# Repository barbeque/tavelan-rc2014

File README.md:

# Board files
Made using KiCad 8.0.3

# Current Status
Submitted to JLCPCB (June 2024) not tested yet.

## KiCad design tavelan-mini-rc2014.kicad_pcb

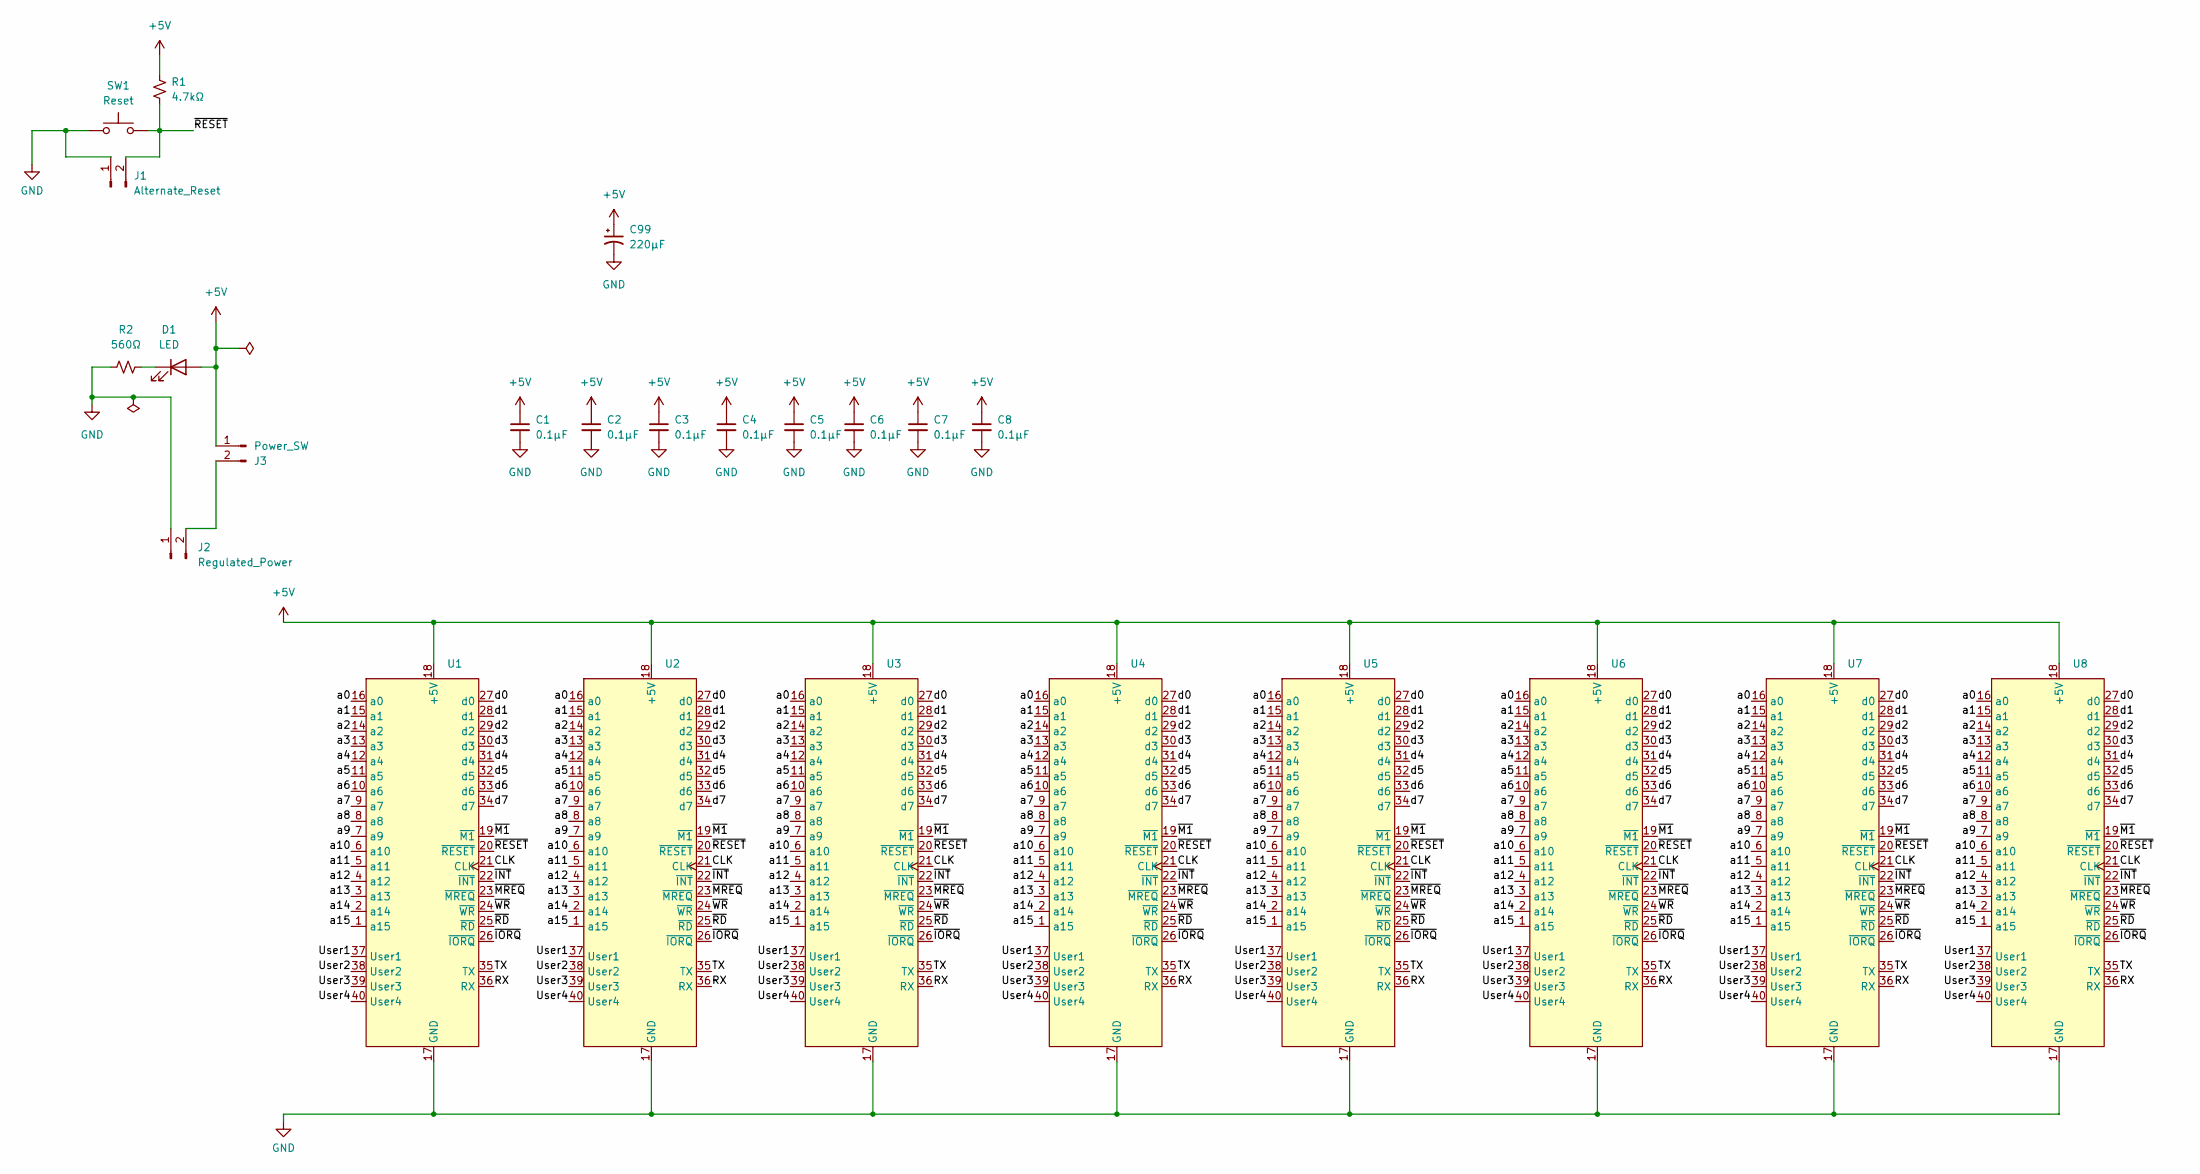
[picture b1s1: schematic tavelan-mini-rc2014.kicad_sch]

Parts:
C1, C2, C3, C4, C5, C6, C7, C8: 0.1µF; C_Disc_D5.0mm_W2.5mm_P5.00mm
C99: 220µF; CP_Radial_D8.0mm_P3.80mm
D1: LED; LED_D3.0mm
J1: Alternate_Reset; TerminalBlock_TE_282834-2_1x02_P2.54mm_Horizontal
J2: Regulated_Power; TerminalBlock_TE_282834-2_1x02_P2.54mm_Horizontal
J3: Power_SW; TerminalBlock_TE_282834-2_1x02_P2.54mm_Horizontal
R1: 4.7kΩ; R_Axial_DIN0207_L6.3mm_D2.5mm_P10.16mm_Horizontal
R2: 560Ω; R_Axial_DIN0207_L6.3mm_D2.5mm_P10.16mm_Horizontal
SW1: Reset; SW_PUSH_6mm
U1, U2, U3, U4, U5, U6, U7, U8: PinSocket_1x40_P2.54mm_Vertical

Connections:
+5V: C1.1, C2.1, C3.1, C4.1, C5.1, C6.1, C7.1, C8.1, C99.1, D1.2 (A), J3.1, R1.1, U1.18 (+5V), U2.18 (+5V), U3.18 (+5V), U4.18 (+5V), U5.18 (+5V), U6.18 (+5V), U7.18 (+5V), U8.18 (+5V)
/CLK: U1.21 (CLK), U2.21 (CLK), U3.21 (CLK), U4.21 (CLK), U5.21 (CLK), U6.21 (CLK), U7.21 (CLK), U8.21 (CLK)
/RX: U1.36 (RX), U2.36 (RX), U3.36 (RX), U4.36 (RX), U5.36 (RX), U6.36 (RX), U7.36 (RX), U8.36 (RX)
/TX: U1.35 (TX), U2.35 (TX), U3.35 (TX), U4.35 (TX), U5.35 (TX), U6.35 (TX), U7.35 (TX), U8.35 (TX)
/User1: U1.37 (User1), U2.37 (User1), U3.37 (User1), U4.37 (User1), U5.37 (User1), U6.37 (User1), U7.37 (User1), U8.37 (User1)
/User2: U1.38 (User2), U2.38 (User2), U3.38 (User2), U4.38 (User2), U5.38 (User2), U6.38 (User2), U7.38 (User2), U8.38 (User2)
/User3: U1.39 (User3), U2.39 (User3), U3.39 (User3), U4.39 (User3), U5.39 (User3), U6.39 (User3), U7.39 (User3), U8.39 (User3)
/User4: U1.40 (User4), U2.40 (User4), U3.40 (User4), U4.40 (User4), U5.40 (User4), U6.40 (User4), U7.40 (User4), U8.40 (User4)
/a0: U1.16 (a0), U2.16 (a0), U3.16 (a0), U4.16 (a0), U5.16 (a0), U6.16 (a0), U7.16 (a0), U8.16 (a0)
/a1: U1.15 (a1), U2.15 (a1), U3.15 (a1), U4.15 (a1), U5.15 (a1), U6.15 (a1), U7.15 (a1), U8.15 (a1)
/a2: U1.14 (a2), U2.14 (a2), U3.14 (a2), U4.14 (a2), U5.14 (a2), U6.14 (a2), U7.14 (a2), U8.14 (a2)
/a3: U1.13 (a3), U2.13 (a3), U3.13 (a3), U4.13 (a3), U5.13 (a3), U6.13 (a3), U7.13 (a3), U8.13 (a3)
/a4: U1.12 (a4), U2.12 (a4), U3.12 (a4), U4.12 (a4), U5.12 (a4), U6.12 (a4), U7.12 (a4), U8.12 (a4)
/a5: U1.11 (a5), U2.11 (a5), U3.11 (a5), U4.11 (a5), U5.11 (a5), U6.11 (a5), U7.11 (a5), U8.11 (a5)
/a6: U1.10 (a6), U2.10 (a6), U3.10 (a6), U4.10 (a6), U5.10 (a6), U6.10 (a6), U7.10 (a6), U8.10 (a6)
/a7: U1.9 (a7), U2.9 (a7), U3.9 (a7), U4.9 (a7), U5.9 (a7), U6.9 (a7), U7.9 (a7), U8.9 (a7)
/a8: U1.8 (a8), U2.8 (a8), U3.8 (a8), U4.8 (a8), U5.8 (a8), U6.8 (a8), U7.8 (a8), U8.8 (a8)
/a9: U1.7 (a9), U2.7 (a9), U3.7 (a9), U4.7 (a9), U5.7 (a9), U6.7 (a9), U7.7 (a9), U8.7 (a9)
/a10: U1.6 (a10), U2.6 (a10), U3.6 (a10), U4.6 (a10), U5.6 (a10), U6.6 (a10), U7.6 (a10), U8.6 (a10)
/a11: U1.5 (a11), U2.5 (a11), U3.5 (a11), U4.5 (a11), U5.5 (a11), U6.5 (a11), U7.5 (a11), U8.5 (a11)
/a12: U1.4 (a12), U2.4 (a12), U3.4 (a12), U4.4 (a12), U5.4 (a12), U6.4 (a12), U7.4 (a12), U8.4 (a12)
/a13: U1.3 (a13), U2.3 (a13), U3.3 (a13), U4.3 (a13), U5.3 (a13), U6.3 (a13), U7.3 (a13), U8.3 (a13)
/a14: U1.2 (a14), U2.2 (a14), U3.2 (a14), U4.2 (a14), U5.2 (a14), U6.2 (a14), U7.2 (a14), U8.2 (a14)
/a15: U1.1 (a15), U2.1 (a15), U3.1 (a15), U4.1 (a15), U5.1 (a15), U6.1 (a15), U7.1 (a15), U8.1 (a15)
/d0: U1.27 (d0), U2.27 (d0), U3.27 (d0), U4.27 (d0), U5.27 (d0), U6.27 (d0), U7.27 (d0), U8.27 (d0)
/d1: U1.28 (d1), U2.28 (d1), U3.28 (d1), U4.28 (d1), U5.28 (d1), U6.28 (d1), U7.28 (d1), U8.28 (d1)
/d2: U1.29 (d2), U2.29 (d2), U3.29 (d2), U4.29 (d2), U5.29 (d2), U6.29 (d2), U7.29 (d2), U8.29 (d2)
/d3: U1.30 (d3), U2.30 (d3), U3.30 (d3), U4.30 (d3), U5.30 (d3), U6.30 (d3), U7.30 (d3), U8.30 (d3)
/d4: U1.31 (d4), U2.31 (d4), U3.31 (d4), U4.31 (d4), U5.31 (d4), U6.31 (d4), U7.31 (d4), U8.31 (d4)
/d5: U1.32 (d5), U2.32 (d5), U3.32 (d5), U4.32 (d5), U5.32 (d5), U6.32 (d5), U7.32 (d5), U8.32 (d5)
/d6: U1.33 (d6), U2.33 (d6), U3.33 (d6), U4.33 (d6), U5.33 (d6), U6.33 (d6), U7.33 (d6), U8.33 (d6)
/d7: U1.34 (d7), U2.34 (d7), U3.34 (d7), U4.34 (d7), U5.34 (d7), U6.34 (d7), U7.34 (d7), U8.34 (d7)
/~INT: U1.22 (~INT), U2.22 (~INT), U3.22 (~INT), U4.22 (~INT), U5.22 (~INT), U6.22 (~INT), U7.22 (~INT), U8.22 (~INT)
/~IORQ: U1.26 (~IORQ), U2.26 (~IORQ), U3.26 (~IORQ), U4.26 (~IORQ), U5.26 (~IORQ), U6.26 (~IORQ), U7.26 (~IORQ), U8.26 (~IORQ)
/~M1: U1.19 (~M1), U2.19 (~M1), U3.19 (~M1), U4.19 (~M1), U5.19 (~M1), U6.19 (~M1), U7.19 (~M1), U8.19 (~M1)
/~MREQ: U1.23 (~MREQ), U2.23 (~MREQ), U3.23 (~MREQ), U4.23 (~MREQ), U5.23 (~MREQ), U6.23 (~MREQ), U7.23 (~MREQ), U8.23 (~MREQ)
/~RD: U1.25 (~RD), U2.25 (~RD), U3.25 (~RD), U4.25 (~RD), U5.25 (~RD), U6.25 (~RD), U7.25 (~RD), U8.25 (~RD)
/~RESET: J1.2, R1.2, SW1.2, U1.20 (~RESET), U2.20 (~RESET), U3.20 (~RESET), U4.20 (~RESET), U5.20 (~RESET), U6.20 (~RESET), U7.20 (~RESET), U8.20 (~RESET)
/~WR: U1.24 (~WR), U2.24 (~WR), U3.24 (~WR), U4.24 (~WR), U5.24 (~WR), U6.24 (~WR), U7.24 (~WR), U8.24 (~WR)
GND: C1.2, C2.2, C3.2, C4.2, C5.2, C6.2, C7.2, C8.2, C99.2, J1.1, J2.1, R2.1, SW1.1, U1.17 (GND), U2.17 (GND), U3.17 (GND), U4.17 (GND), U5.17 (GND), U6.17 (GND), U7.17 (GND), U8.17 (GND)
unnamed: D1.1 (K), R2.2
unnamed: J2.2, J3.2

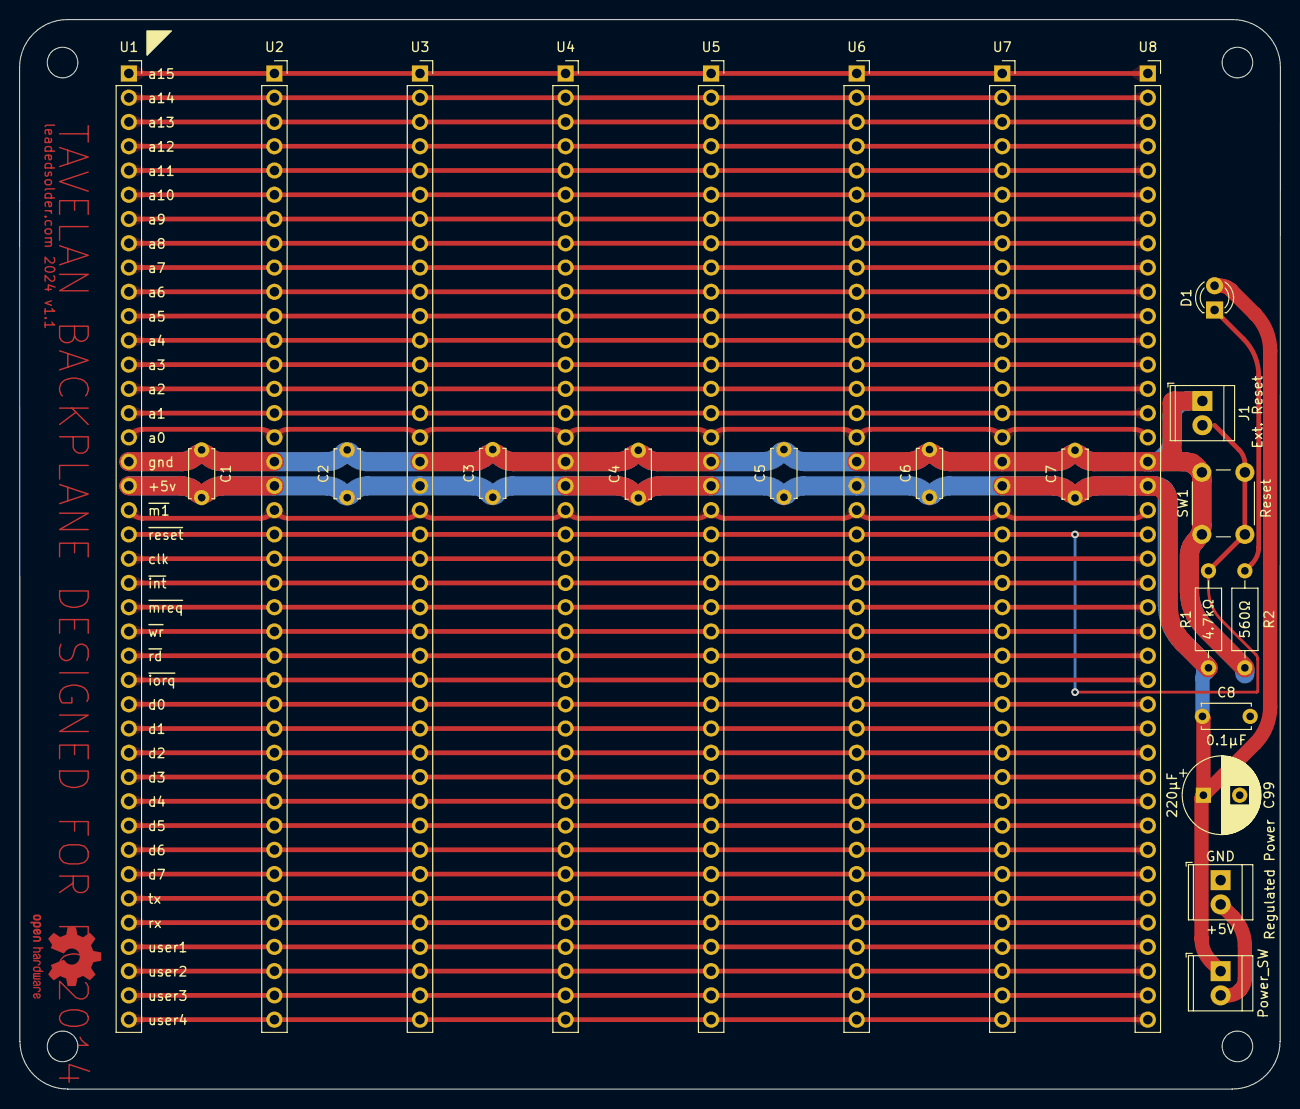
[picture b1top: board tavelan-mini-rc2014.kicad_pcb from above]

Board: 2 copper layers, 132.0 x 112.0 mm, 24 parts (0 on the bottom side), 42 nets.

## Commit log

2024-06-24 Outline
2024-06-24 V1 to JLCPCB
2024-06-24 Round tracks, of course
2024-06-24 V1 really, really released to JLCPCB
2024-06-24 OSHW logo
2024-06-24 Progress
2024-06-25 Upgrade to KiCad 8
2024-06-25 Version in README
2024-07-11 Add 5V and GND traces to the back, too
2024-07-11 Route reset trace in a way that doesn't screw up power
2025-02-02 Ground pour; add power switch header
